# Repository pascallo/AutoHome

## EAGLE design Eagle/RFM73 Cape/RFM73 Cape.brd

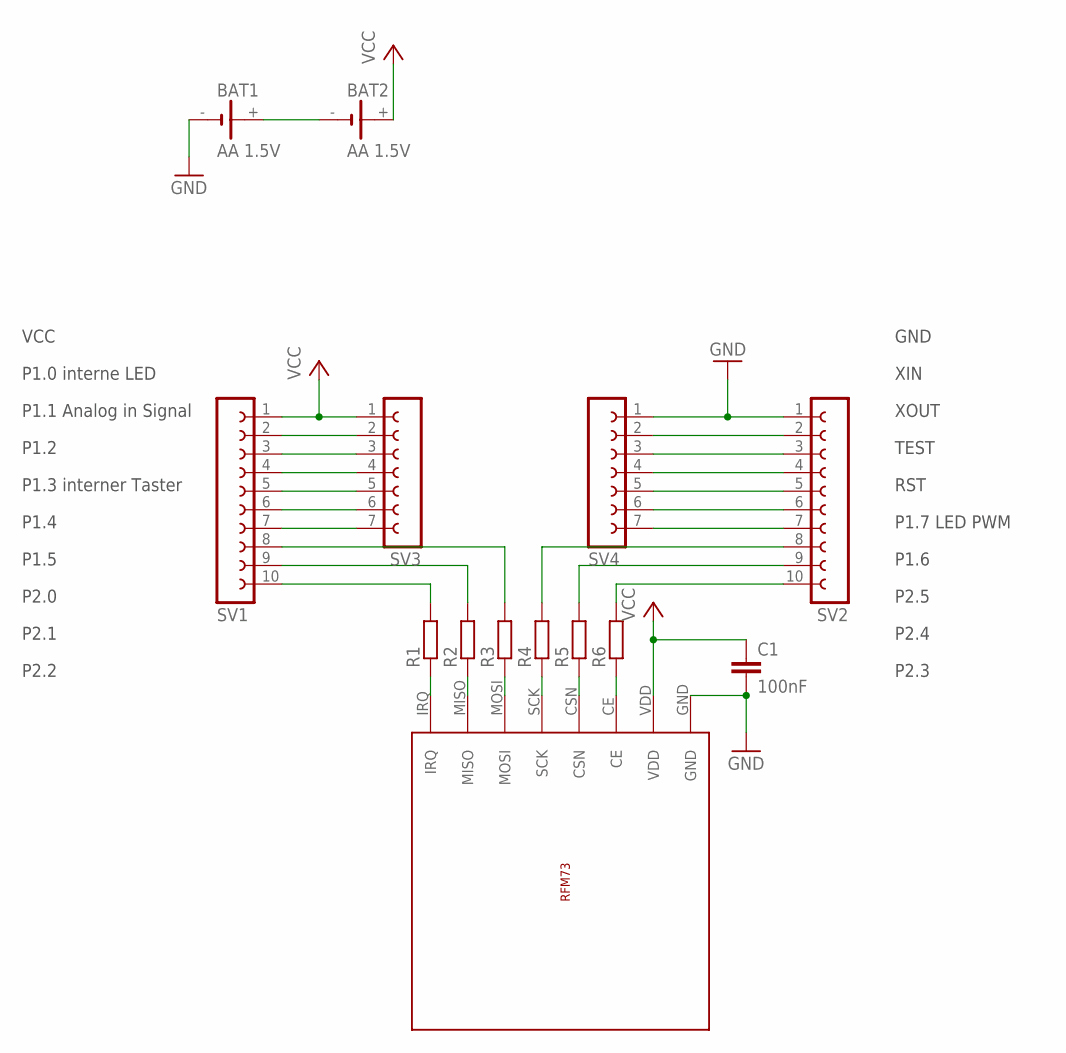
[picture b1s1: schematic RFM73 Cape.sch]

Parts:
BAT1, BAT2: AA 1.5V; SL-160AA/PR
C1: 100nF; C0805
R1, R2, R3, R4, R5, R6: R-EU_R0805W; R0805W
SV1, SV2: FE10-1; FE10
SV3, SV4: FE07-1; FE07
U$1: RFM73

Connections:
GND: BAT1.-, C1.2, SV2.1, SV4.1, U$1.GND
unnamed: R1.2, SV1.10
unnamed: BAT1.+, BAT2.-
unnamed: R2.2, SV1.9
unnamed: R3.2, SV1.8
unnamed: R4.2, SV2.8
unnamed: R5.2, SV2.9
unnamed: R6.2, SV2.10
unnamed: SV1.2, SV3.2
unnamed: SV1.3, SV3.3
unnamed: SV1.4, SV3.4
unnamed: SV1.5, SV3.5
unnamed: SV1.6, SV3.6
unnamed: SV1.7, SV3.7
unnamed: SV2.2, SV4.2
unnamed: SV2.3, SV4.3
unnamed: SV2.4, SV4.4
unnamed: SV2.5, SV4.5
unnamed: SV2.6, SV4.6
unnamed: SV2.7, SV4.7
unnamed: R1.1, U$1.IRQ
unnamed: R2.1, U$1.MISO
unnamed: R3.1, U$1.MOSI
unnamed: R4.1, U$1.SCK
unnamed: R5.1, U$1.CSN
unnamed: R6.1, U$1.CE
VCC: BAT2.+, C1.1, SV1.1, SV3.1, U$1.VDD

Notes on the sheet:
P1.0 interne LED
P1.1 Analog in Signal
P1.2
P1.3 interner Taster
VCC
P1.4
P2.0
P2.1
P2.2
GND
XIN
XOUT
TEST
RST
P1.7 LED PWM
P1.6
P2.5
P2.4
P2.3
P1.5

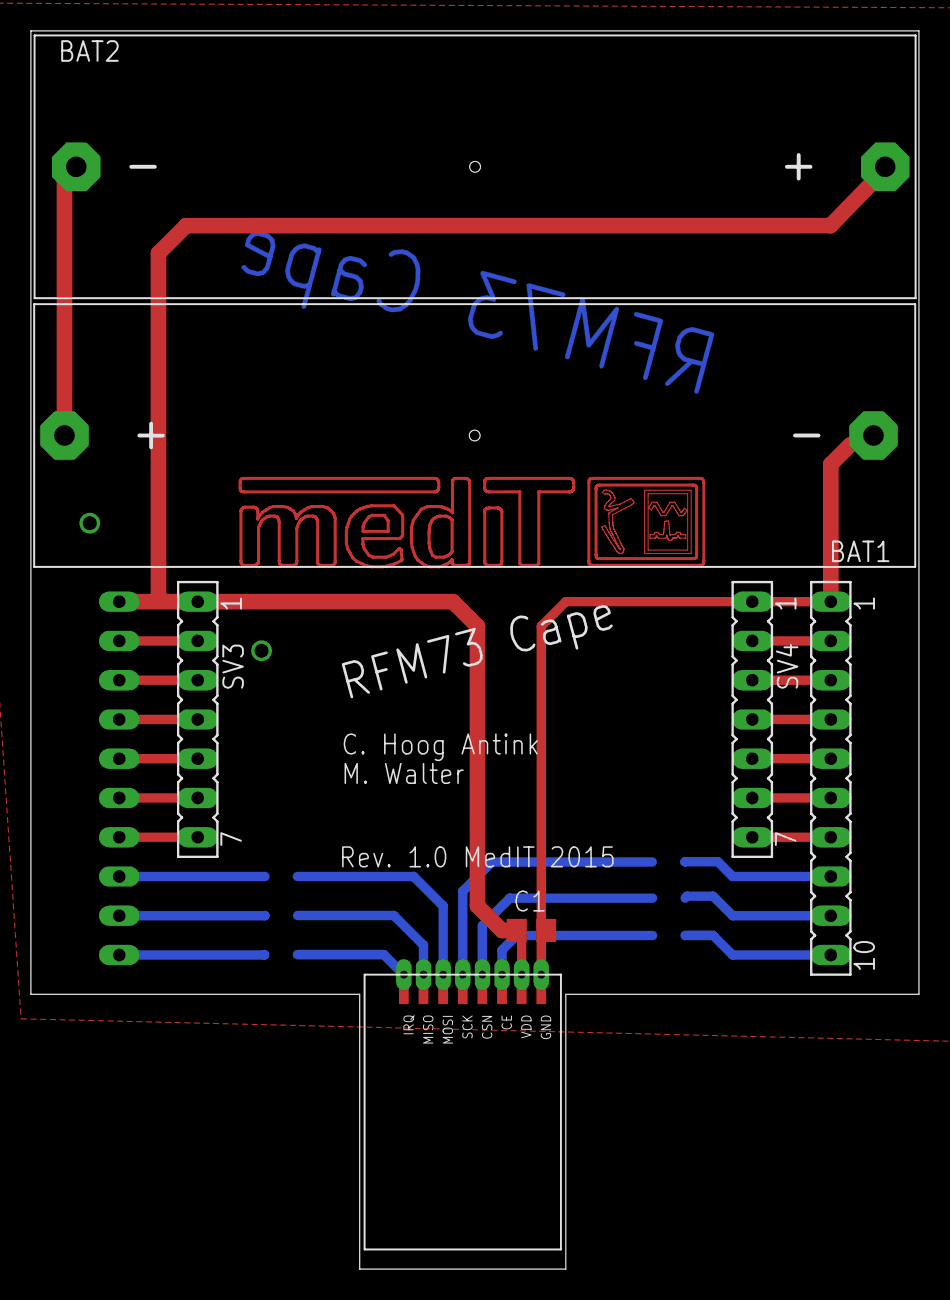
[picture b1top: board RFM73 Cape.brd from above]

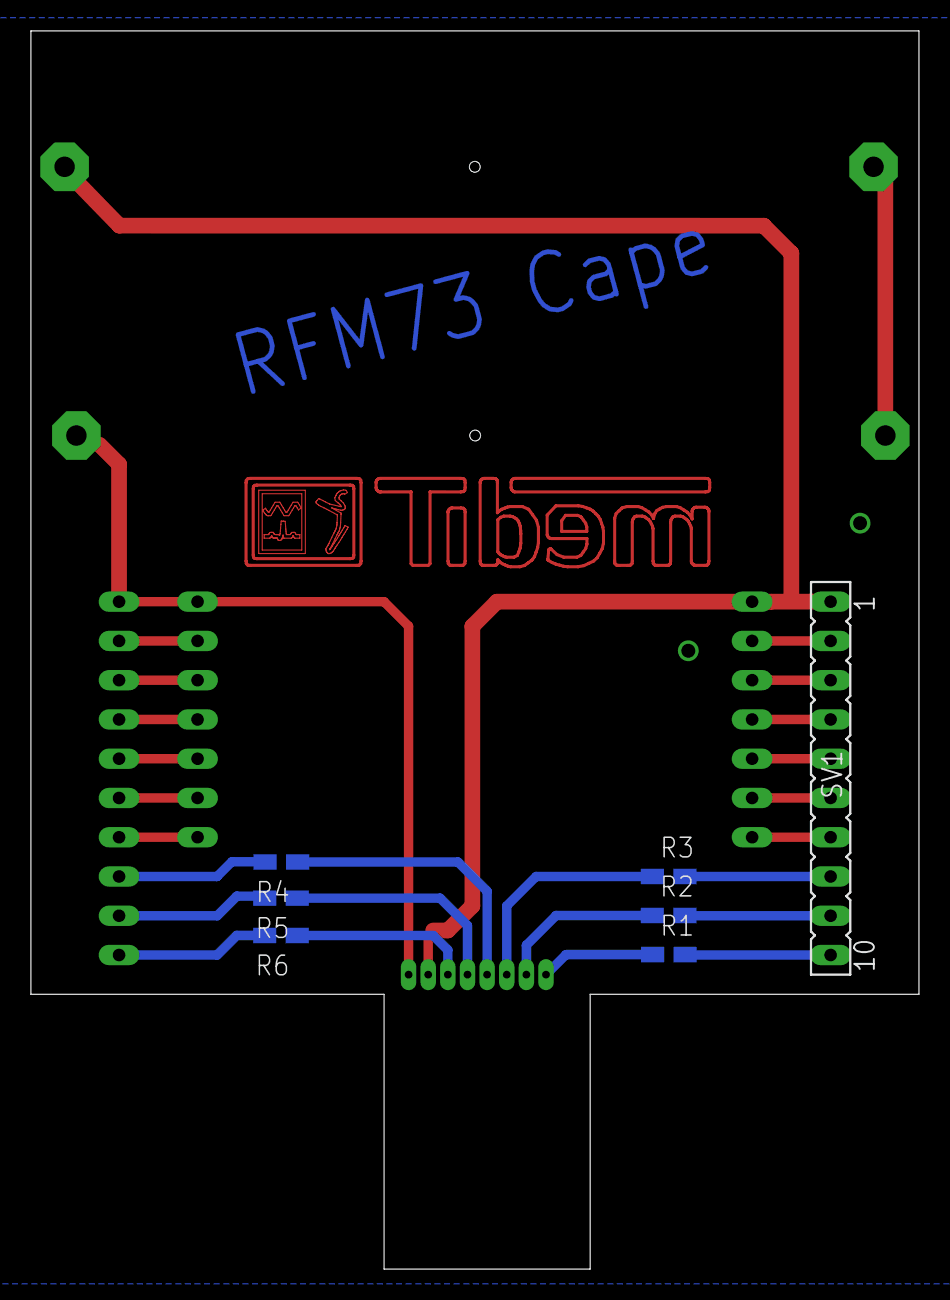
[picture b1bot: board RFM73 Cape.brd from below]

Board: 2 copper layers, 57.5 x 80.1 mm, 15 parts (7 on the bottom side), 27 nets.

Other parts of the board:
U$2: MEDIT

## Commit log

2015-11-04 Init MSP Code
2015-11-04 clean up + git ignore
2015-11-04 rename .gitignore to work properly
2015-11-05 clean master
2015-11-05 clean sensor A
2015-11-05 Add RFM73 Eagle Layout
